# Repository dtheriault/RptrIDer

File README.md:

# RptrIDer

Teensy3.2 Based Repeater Controller

This is a very simplistic repeater controller I built for Sherwin WB7NFX.
Included in the project is manual, schematic, eagle board files and the
Arduino sketch file for a Teensy3.2 board.

The repeater controller was designed to interface to a Westel DRB25 VHF
repeater.  This repeater did not have capability to ID per FCC Part 97 rules
and since the machine was to be used on the 2m ham band, this was a must.

Sherwin wanted the repeater to generate a Voice ID and provided me with a
small PCB that performed audio recording and playback.  I decided to build up
this board and have it controlled by a small ATtiny85 processor.  Shortly I
wanted to add CW support and have more input/outputs for buttons and LED's
so moved to an Teensy3.2 board I had purchased but had not found a project
to use it with.  A repeater controller seemed ideal.

Front panel was to have LED's to indicate status of the repeater and
controller operations.  When PTT, CW ID, Voice ID, Carrier Detect and status
for when the Voice Recording is erased or recorded.  There's also a heartbeat
and init status LED.

Interface to the repeater is via an RJ45 jack on the transceiver card.
There was an empty set of slots in the chassis for me to add a panel, speaker
microphone jack, LED's, buttons and switches and a volume control.  It also
mounts a home brew PCB that houses the Teensy and Voice ID boards.

The board is very simple 3 channel audio mixer with header for the Teensy3.2
and a voice ID board.  Uses standard header pins since that's what I had and
allowed me to debug this on the desk vs. connected to the repeater.

The Teensy3.2 is responsible for time keeping, generating a CW ID, detecting
inputs such as PTT, and front panel buttons and implements simplistic Carrier
Detect to know when the repeater is in use.  Westel did not have COS line
for me to use.  Power for the board is supplied by the transceiver card and
total current at 12v is around 150ma max.

There is a directory with photo's of the project, and if you search on
YouTube you can find a movie of the prototype in use during debug of the
project.

Special thanks goes to SV1DJG, Nick in Greece who developed the CW Beacon
sketch I leveraged into this project.

This project is available via GPL for your use.

Feel free to drop me an email if you have any questions on the project and
I'll try to answer them as best I can.  Please note, the code was quickly
developed and is probably still has a bug or two.

WB7NFX Repeater is operational in Chino Valley Az @ 144.570/145.170 Mhz with
PL of 100.0 Hz.

73,
Doug - NO1D

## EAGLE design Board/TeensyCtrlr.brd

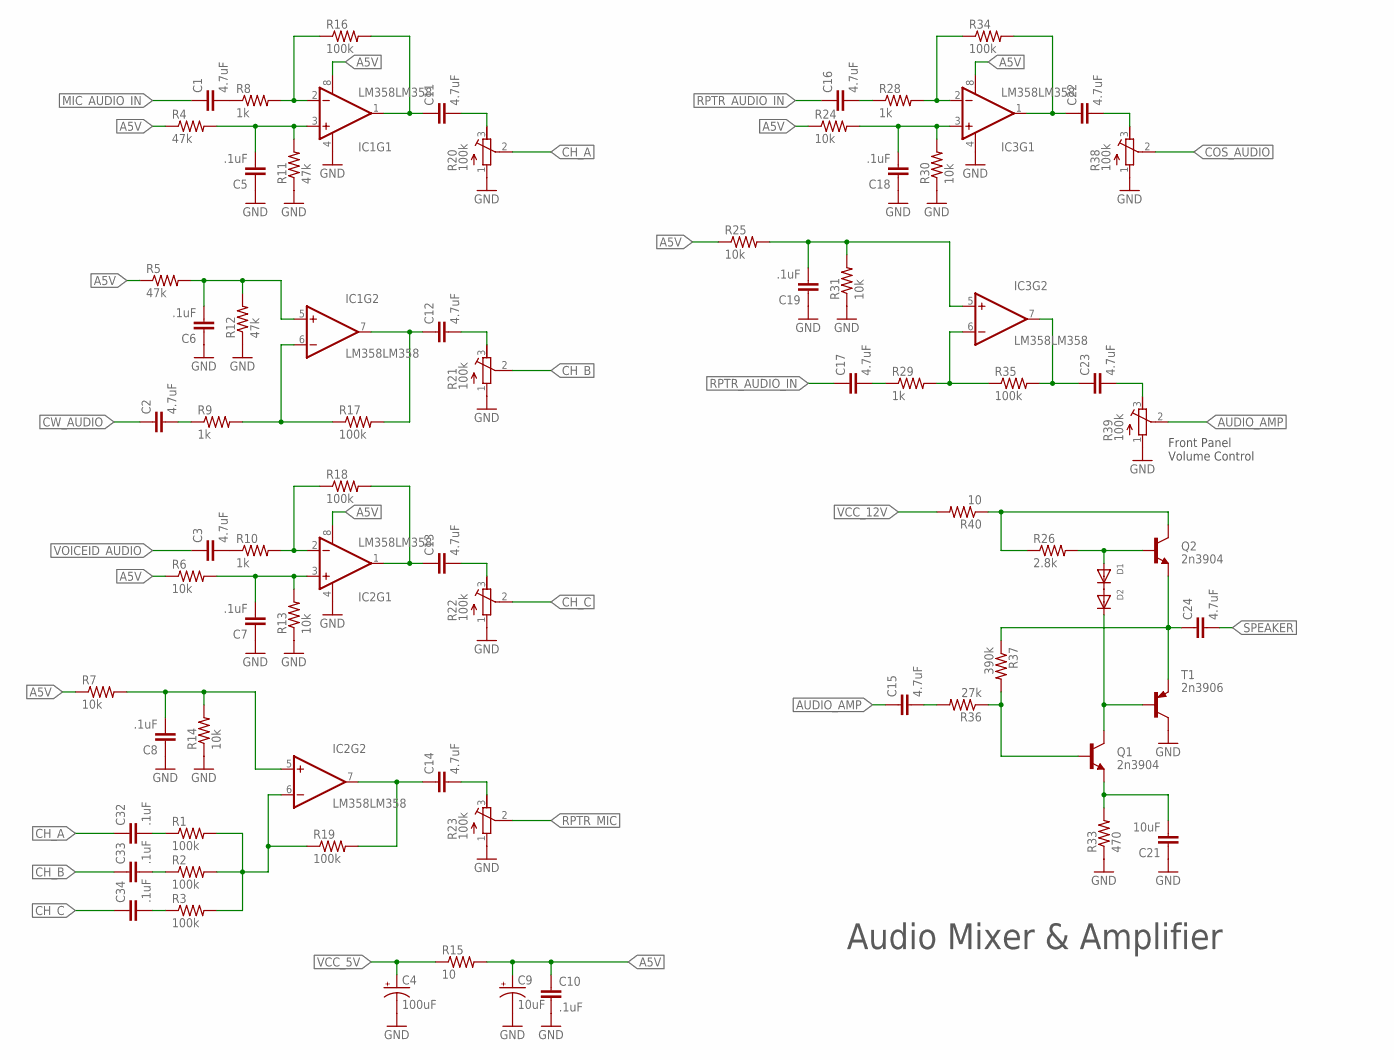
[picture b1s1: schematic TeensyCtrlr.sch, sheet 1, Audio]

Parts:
C1, C2, C3, C11, C12, C13, C14, C16, C17, C22, C23: 4.7uF; CAP-PTH-SMALL2
C4: 100uF; CPOL-RADIAL-10UF-25V
C5, C6, C7, C8, C10, C18, C19, C32, C33, C34: .1uF; 0805
C9: 10uF; CPOL-RADIAL-100UF-25V
C15, C24: 4.7uF; CAP-PTH-SMALL
C21: 10uF; CAP-PTH-SMALL
D1, D2: DIODEDO-1N4148; DO-1N4148
IC1, IC2, IC3: LM358LM358; SOIC8
Q1, Q2: 2n3904; TO-92-AMMO
R1, R2, R3, R16, R17, R18, R19, R34, R35: 100k; 0805
R4, R5, R11, R12: 47k; 0805
R6, R7, R13, R14, R24, R25, R30, R31: 10k; 0805
R8, R9, R10, R28, R29: 1k; 0805
R15, R40: 10; 0805
R20, R21, R22, R23, R38, R39: 100k; RTRIM3339P
R26: 2.8k; 0805
R33: 470; 0805
R36: 27k; 0805
R37: 390k; 0805
T1: 2n3906; TO92-EBC

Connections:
A5V: C9.1 (+), C10.1, IC1.8 (V+), IC2.8 (V+), IC3.8 (V+), R4.1, R5.1, R6.1, R7.1, R15.2, R24.1, R25.1
AUDIO_AMP: C15.1, R39.2 (S)
CH_A: C32.1, R20.2 (S)
CH_B: C33.1, R21.2 (S)
CH_C: C34.1, R22.2 (S)
COS_AUDIO: R38.2 (S); also elsewhere on the board
CW_AUDIO: C2.1; also elsewhere on the board
GND: C4.2 (-), C5.1, C6.1, C7.1, C8.1, C9.2 (-), C10.2, C18.1, C19.1, C21.1, IC1.4 (V-), IC2.4 (V-), IC3.4 (V-), R11.1, R12.1, R13.1, R14.1, R20.1 (A), R21.1 (A), R22.1 (A), R23.1 (A), R30.1, R31.1, R33.1, R38.1 (A), R39.1 (A), T1.C; also elsewhere on the board
MIC_AUDIO_IN: C1.1; also elsewhere on the board
unnamed: IC1.2 (-IN), R8.2, R16.1
unnamed: C5.2, IC1.3 (+IN), R4.2, R11.2
unnamed: C1.2, R8.1
unnamed: C11.2, R20.3 (E)
unnamed: IC1.6 (-IN), R9.2, R17.1
unnamed: C11.1, IC1.1 (OUT), R16.2
unnamed: IC2.2 (-IN), R10.2, R18.1
unnamed: C6.2, IC1.5 (+IN), R5.2, R12.2
unnamed: C2.2, R9.1
unnamed: C12.1, IC1.7 (OUT), R17.2
unnamed: C12.2, R21.3 (E)
unnamed: C7.2, IC2.3 (+IN), R6.2, R13.2
unnamed: C3.2, R10.1
unnamed: C13.1, IC2.1 (OUT), R18.2
unnamed: C13.2, R22.3 (E)
unnamed: IC2.6 (-IN), R1.2, R2.2, R3.2, R19.1
unnamed: C8.2, IC2.5 (+IN), R7.2, R14.2
unnamed: C15.2, R36.2
unnamed: C14.1, IC2.7 (OUT), R19.2
unnamed: C14.2, R23.3 (E)
unnamed: Q2.3 (C), R26.1, R40.1
unnamed: IC3.2 (-IN), R28.2, R34.1
unnamed: C21.2, Q1.1 (E), R33.2
unnamed: C18.2, IC3.3 (+IN), R24.2, R30.2
unnamed: C16.2, R28.1
unnamed: C22.1, IC3.1 (OUT), R34.2
unnamed: C22.2, R38.3 (E)
unnamed: IC3.6 (-IN), R29.2, R35.1
unnamed: C19.2, IC3.5 (+IN), R25.2, R31.2
unnamed: C17.2, R29.1
unnamed: C23.1, IC3.7 (OUT), R35.2
unnamed: C23.2, R39.3 (E)
unnamed: C24.1, Q2.1 (E), R37.1, T1.E
unnamed: D1.C, D2.A
unnamed: D1.A, Q2.2 (B), R26.2
unnamed: D2.C, Q1.3 (C), T1.B
unnamed: C32.2, R1.1
unnamed: C33.2, R2.1
unnamed: C34.2, R3.1
unnamed: Q1.2 (B), R36.1, R37.2
RPTR_AUDIO_IN: C16.1, C17.1; also elsewhere on the board
RPTR_MIC: R23.2 (S); also elsewhere on the board
SPEAKER: C24.2; also elsewhere on the board
VCC_5V: C4.1 (+), R15.1
VCC_12V: R40.2; also elsewhere on the board
VOICEID_AUDIO: C3.1; also elsewhere on the board

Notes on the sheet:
Audio Mixer & Amplifier
Front Panel Volume Control

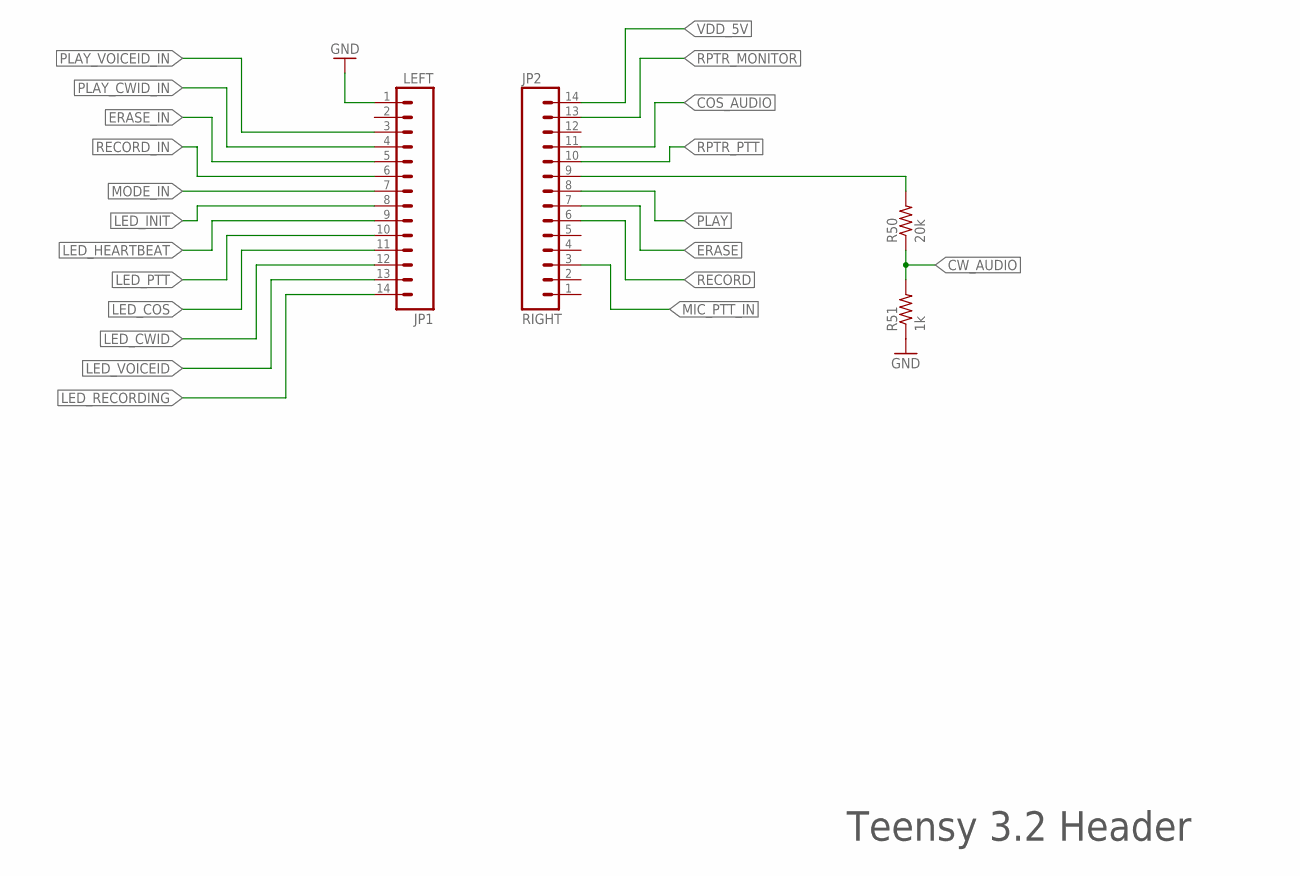
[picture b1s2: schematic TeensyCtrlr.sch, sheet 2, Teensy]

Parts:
JP1: LEFT; 1X14-LONGPADS
JP2: RIGHT; 1X14-LONGPADS
R50: 20k; 0805
R51: 1k; 0805

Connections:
COS_AUDIO: JP2.11; also elsewhere on the board
CW_AUDIO: R50.1, R51.2; also elsewhere on the board
ERASE: JP2.7; also elsewhere on the board
ERASE_IN: JP1.5; also elsewhere on the board
GND: JP1.1, R51.1; also elsewhere on the board
LED_COS: JP1.11; also elsewhere on the board
LED_CWID: JP1.12; also elsewhere on the board
LED_HEARTBEAT: JP1.9; also elsewhere on the board
LED_INIT: JP1.8; also elsewhere on the board
LED_PTT: JP1.10; also elsewhere on the board
LED_RECORDING: JP1.14; also elsewhere on the board
LED_VOICEID: JP1.13; also elsewhere on the board
MIC_PTT_IN: JP2.3; also elsewhere on the board
MODE_IN: JP1.7; also elsewhere on the board
unnamed: JP2.9, R50.2
PLAY: JP2.8; also elsewhere on the board
PLAY_CWID_IN: JP1.4; also elsewhere on the board
PLAY_VOICEID_IN: JP1.3; also elsewhere on the board
RECORD: JP2.6; also elsewhere on the board
RECORD_IN: JP1.6; also elsewhere on the board
RPTR_MONITOR: JP2.13; also elsewhere on the board
RPTR_PTT: JP2.10; also elsewhere on the board
VDD_5V: JP2.14; also elsewhere on the board

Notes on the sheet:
Teensy 3.2 Header

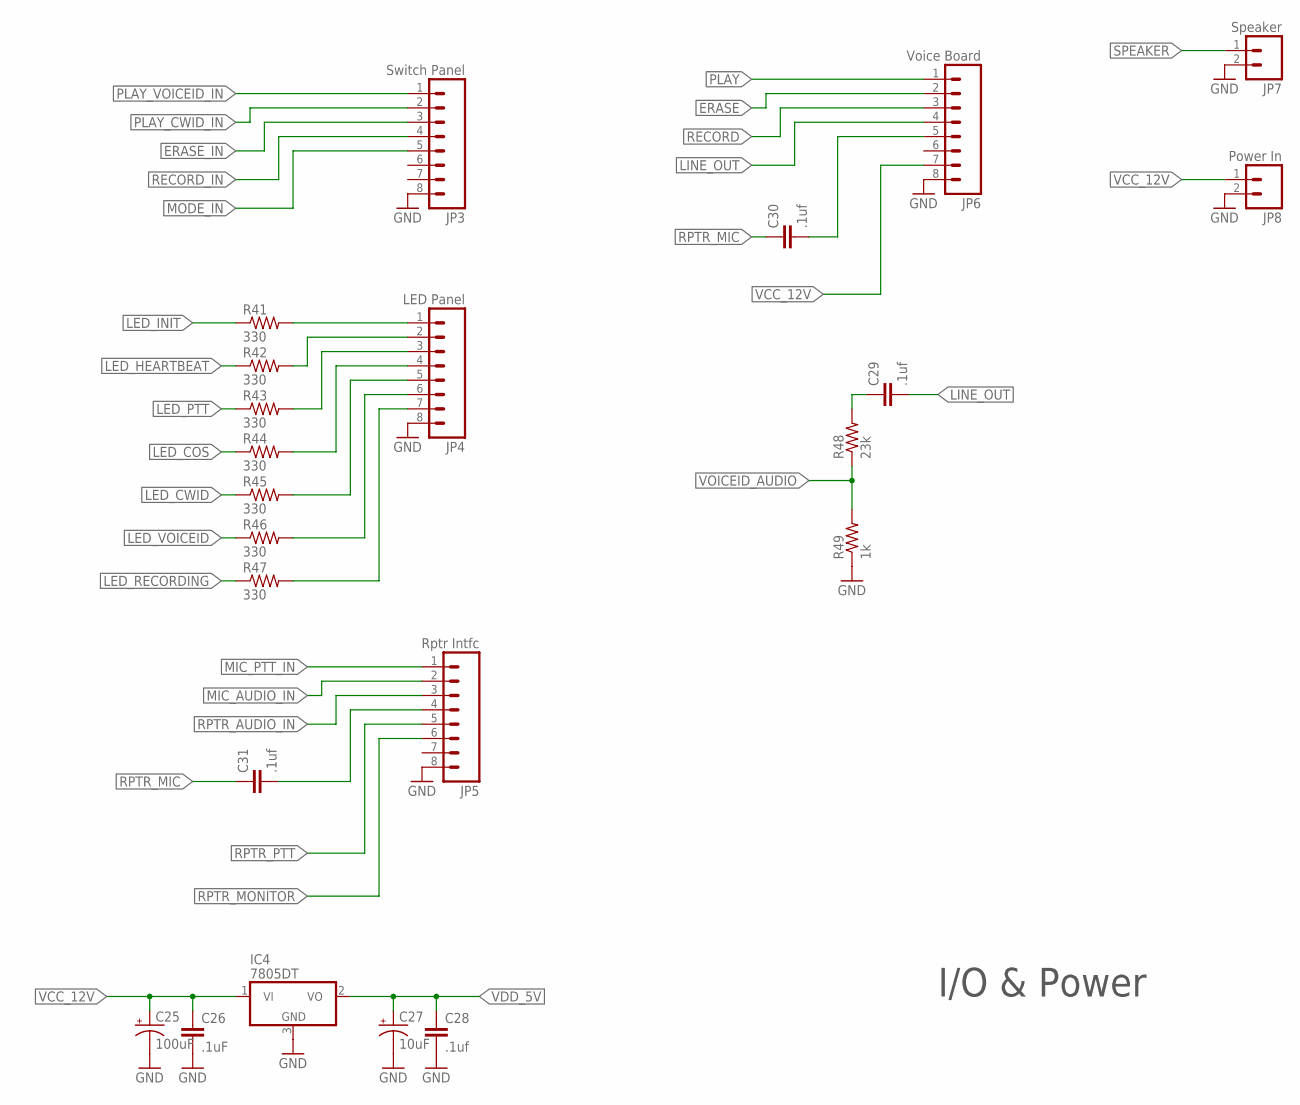
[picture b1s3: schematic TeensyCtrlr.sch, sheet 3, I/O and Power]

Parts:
C25: 100uF; CPOL-RADIAL-1000UF-25V
C26: .1uF; 0805
C27: 10uF; CPOL-RADIAL-100UF-25V
C28, C29, C30, C31: .1uf; 0805
IC4: 7805DT; TO252
JP3: Switch Panel; 1X08_LONGPADS
JP4: LED Panel; 1X08_LONGPADS
JP5: Rptr Intfc; 1X08_LONGPADS
JP6: Voice Board; 1X08_LONGPADS
JP7: Speaker; 1X02_LONGPADS
JP8: Power In; 1X02_LONGPADS
R41, R42, R43, R44, R45, R46, R47: 330; 0805
R48: 23k; 0805
R49: 1k; 0805

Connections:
ERASE: JP6.2; also elsewhere on the board
ERASE_IN: JP3.3; also elsewhere on the board
GND: C25.-, C26.2, C27.2 (-), C28.2, IC4.3 (GND), JP3.8, JP4.8, JP5.8, JP6.8, JP7.2, JP8.2, R49.1; also elsewhere on the board
LED_COS: R44.1; also elsewhere on the board
LED_CWID: R45.1; also elsewhere on the board
LED_HEARTBEAT: R42.1; also elsewhere on the board
LED_INIT: R41.1; also elsewhere on the board
LED_PTT: R43.1; also elsewhere on the board
LED_RECORDING: R47.1; also elsewhere on the board
LED_VOICEID: R46.1; also elsewhere on the board
LINE_OUT: C29.2, JP6.4
MIC_AUDIO_IN: JP5.2; also elsewhere on the board
MIC_PTT_IN: JP5.1; also elsewhere on the board
MODE_IN: JP3.5; also elsewhere on the board
unnamed: JP4.1, R41.2
unnamed: JP4.2, R42.2
unnamed: JP4.3, R43.2
unnamed: JP4.4, R44.2
unnamed: JP4.5, R45.2
unnamed: JP4.6, R46.2
unnamed: JP4.7, R47.2
unnamed: C31.2, JP5.4
unnamed: C30.2, JP6.5
unnamed: C29.1, R48.2
PLAY: JP6.1; also elsewhere on the board
PLAY_CWID_IN: JP3.2; also elsewhere on the board
PLAY_VOICEID_IN: JP3.1; also elsewhere on the board
RECORD: JP6.3; also elsewhere on the board
RECORD_IN: JP3.4; also elsewhere on the board
RPTR_AUDIO_IN: JP5.3; also elsewhere on the board
RPTR_MIC: C30.1, C31.1; also elsewhere on the board
RPTR_MONITOR: JP5.6; also elsewhere on the board
RPTR_PTT: JP5.5; also elsewhere on the board
SPEAKER: JP7.1; also elsewhere on the board
VCC_12V: C25.+, C26.1, IC4.1 (VI), JP6.7, JP8.1; also elsewhere on the board
VDD_5V: C27.1 (+), C28.1, IC4.2 (VO); also elsewhere on the board
VOICEID_AUDIO: R48.1, R49.2; also elsewhere on the board

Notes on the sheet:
I/O & Power

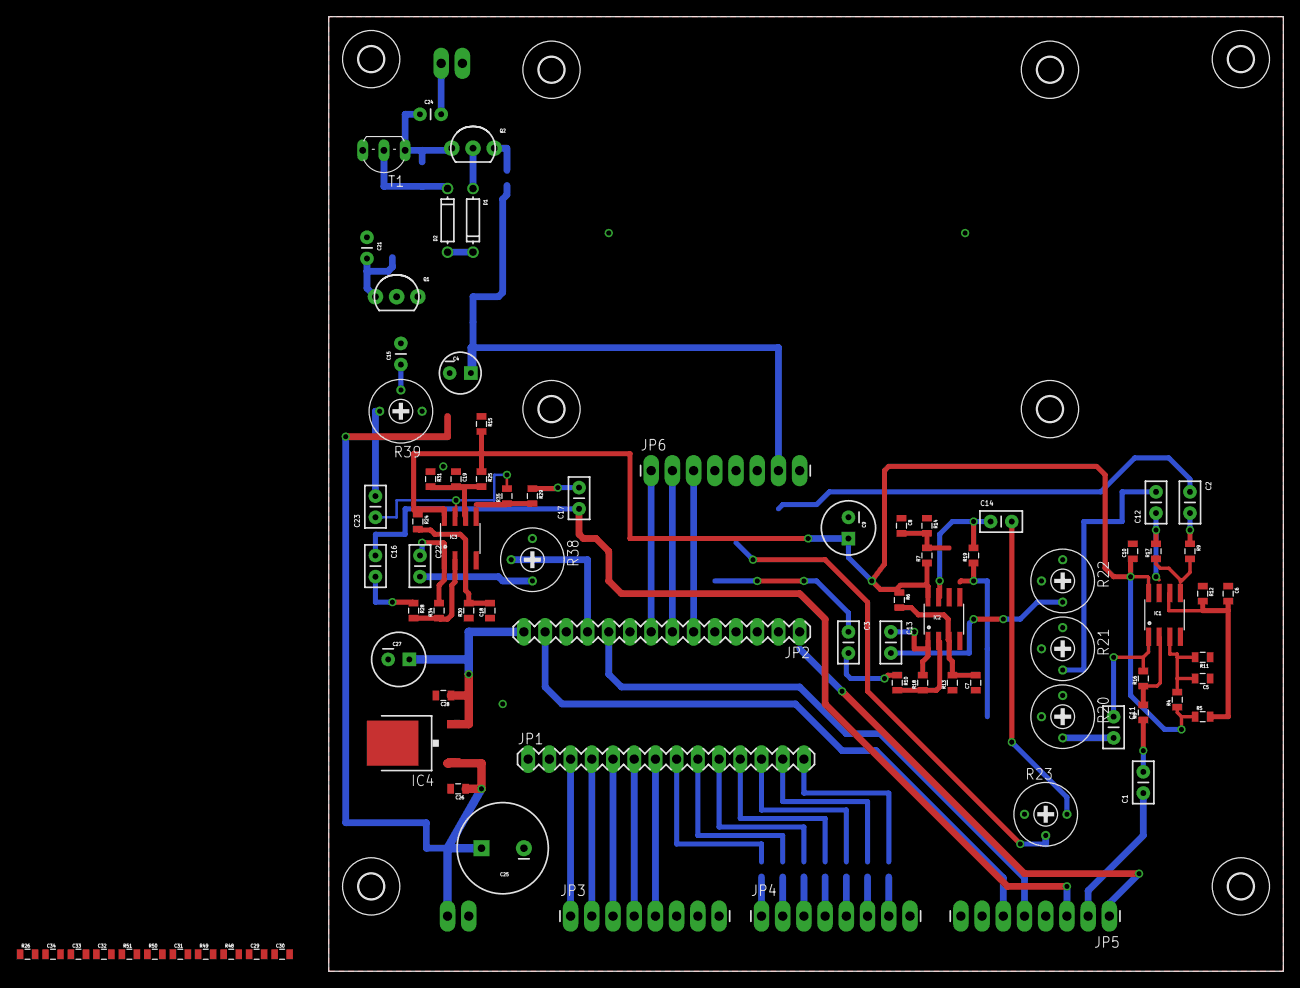
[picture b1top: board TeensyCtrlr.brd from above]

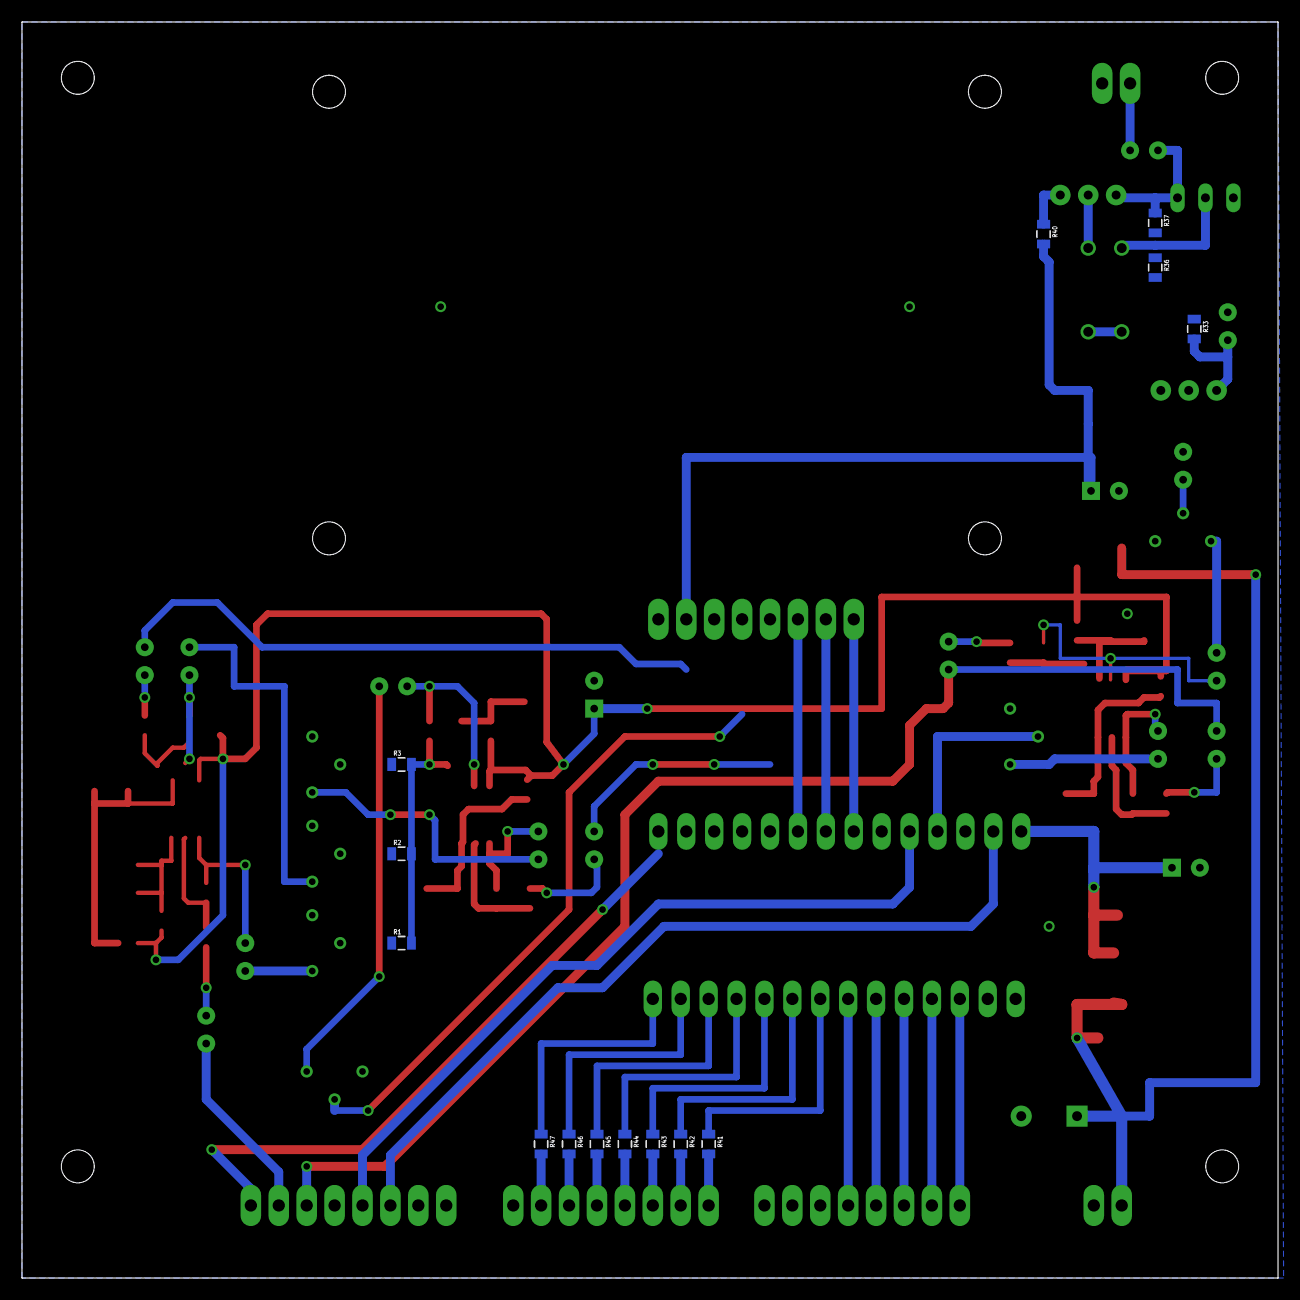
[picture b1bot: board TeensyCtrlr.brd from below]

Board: 2 copper layers, 114.3 x 114.3 mm, 107 parts (14 on the bottom side), 86 nets.

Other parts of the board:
U$1, U$2, U$3, U$4, U$5, U$6, U$7, U$8: 3,0

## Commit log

2017-02-02 Two new pics of front panel
2017-02-02 Source for pdf manual
2017-07-20 Pushing updated sketch files for teensy based repeater controller project.

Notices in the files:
parts and their libraries:
SparkFun-Capacitors: Licensing: Creative Commons ShareAlike 4.0 International - https://creativecommons.org/licenses/by-sa/4.0
